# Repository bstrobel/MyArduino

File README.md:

# MyArduino
PCB to get my stock pile of 328s used as Arduino

Idee: Kleines generisches PCB bei Elecrow bestellten, um meine 328 einfach verbauen oder auf Steckbrett verwenden zu können.
- Größe um in direkt in kleines, günstiges Gehäuse verbaut werden zu können, das es bei Reichelt oder Conrad gibt
	- Gehäuse bei R heraussuchen, wenn Mindestgröße feststeht
- Pin Header mit Belegung und Bezeichnung wie bei Arduino, aber nicht notwendigerweise so angeordnet, dass Arduino Shields darauf passen. Aber eventuell so, dass Einsatz kleiner Shields für SD-Karten oder Sensoren nicht blockiert wird.
- Pin Header so anordnen, dass Verwendung auf Steckbrett möglich ist
- Stromversorgung:
	- Optionale Bestückung mit LM317 inkl. Justier-Rs und Block-Cs
	- auch MCP1702 (LDO 5v) Regler -> Achtung: nicht pinkompatibel mit 78L05!
	- Stromversorgungsheader für direkte Versorgung oder an Regler-IC
- ICP Header mit Standardbelegung
- Resettaster
- Arduino-LED an Port 13 vorsehen, muss ja nicht bestückt werden.
- Quarzbestückung vorsehen
	- aber Ports auch herausführen
- AREF-Cap: https://www.avrfreaks.net/forum/capacitor-aref-atmega328

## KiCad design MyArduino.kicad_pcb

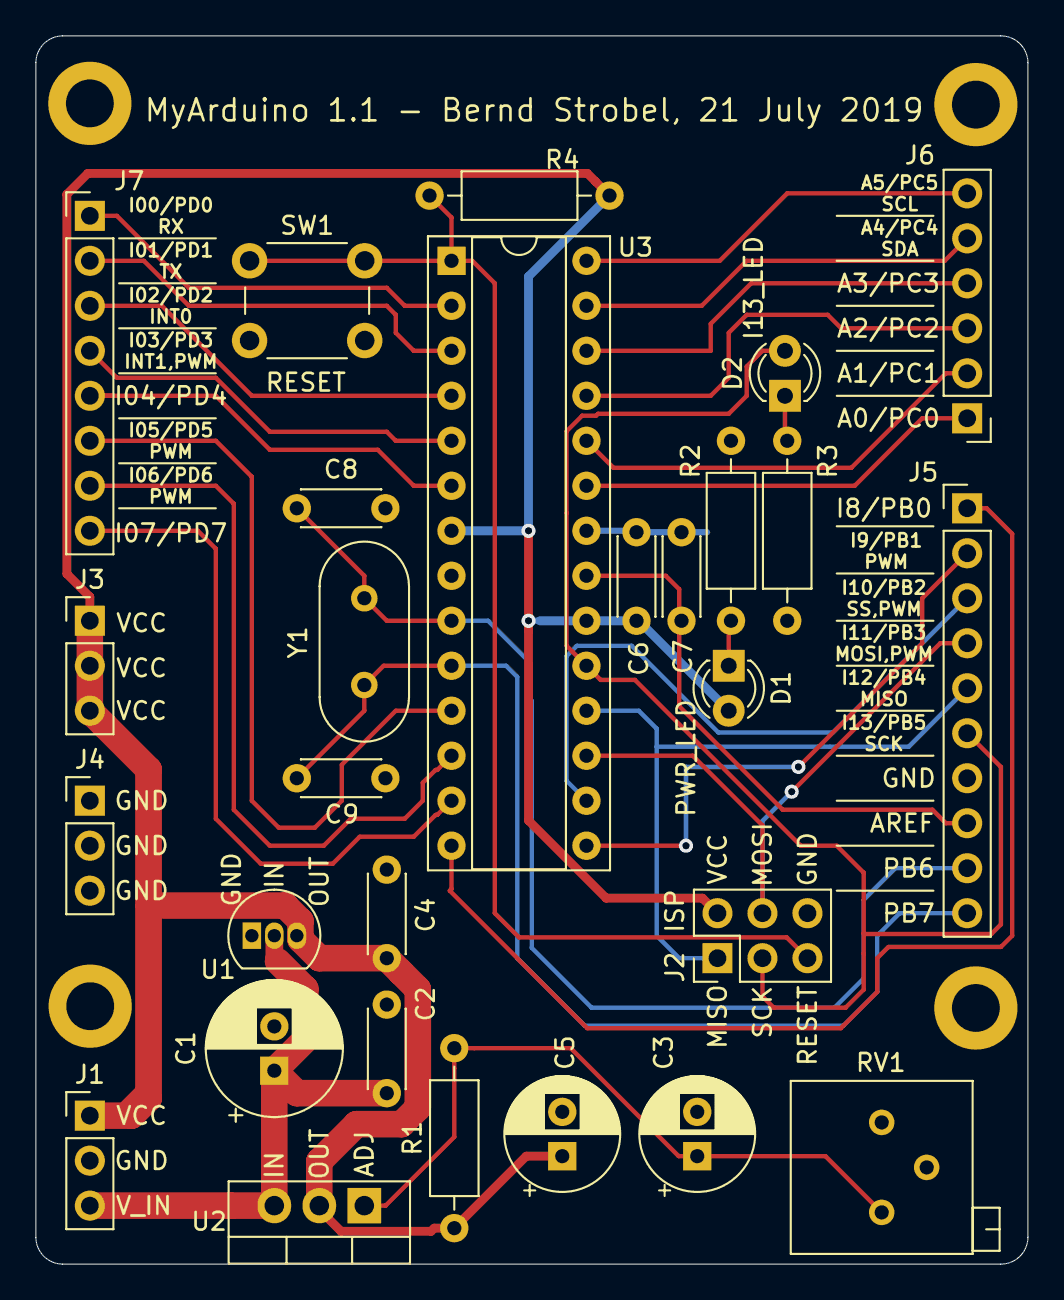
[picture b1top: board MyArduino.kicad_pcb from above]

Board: 2 copper layers, 56.0 x 69.3 mm, 32 parts (0 on the bottom side), 30 nets.

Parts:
C1: 100u; CP_Radial_D7.5mm_P2.50mm
C2, C4, C6: 100n; C_Disc_D4.3mm_W1.9mm_P5.00mm
C3: 10u; CP_Radial_D6.3mm_P2.50mm
C5: 22u; CP_Radial_D6.3mm_P2.50mm
C7: 10n; C_Disc_D4.3mm_W1.9mm_P5.00mm
C8, C9: 22p; C_Disc_D4.3mm_W1.9mm_P5.00mm
D1, D2: LED; LED_D3.0mm
J1: PWR; PinHeader_1x03_P2.54mm_Vertical
J2: ISP; PinHeader_2x03_P2.54mm_Vertical
J3: VCC; PinHeader_1x03_P2.54mm_Vertical
J4: GND; PinHeader_1x03_P2.54mm_Vertical
J5: IOH; PinHeader_1x10_P2.54mm_Vertical
J6: AD; PinHeader_1x06_P2.54mm_Vertical
J7: IOL; PinHeader_1x08_P2.54mm_Vertical
J8, J9, J10, J11: MountingHole_2.7mm_M2.5_DIN965_Pad
R1: 240R; R_Axial_DIN0207_L6.3mm_D2.5mm_P10.16mm_Horizontal
R2, R3: 470R; R_Axial_DIN0207_L6.3mm_D2.5mm_P10.16mm_Horizontal
R4: 10k; R_Axial_DIN0207_L6.3mm_D2.5mm_P10.16mm_Horizontal
RV1: 5k; Potentiometer_Bourns_3296P_Horizontal
SW1: SW_Push; SW_PUSH_6mm_H5mm
U1: MCP1700-5002E_TO92; TO-92_Inline
U2: LM317_TO220; TO-220-3_Vertical
U3: ATmega328P-PU; DIP-28_W7.62mm_Socket
Y1: 16MHz; Crystal_HC18-U_Vertical

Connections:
/AD0: J6.1, U3.23
/AD1: J6.2, U3.24
/AD2: J6.3, U3.25
/AD3: J6.4, U3.26
/AD4: J6.5, U3.27
/AD5: J6.6, U3.28
/AREF: C7.1, J5.8, U3.21
/IO0: J7.1, U3.2
/IO1: J7.2, U3.3
/IO2: J7.3, U3.4
/IO3: J7.4, U3.5
/IO4: J7.5, U3.6
/IO5: J7.6, U3.11
/IO6: J7.7, U3.12
/IO7: J7.8, U3.13
/IO8: J5.1, U3.14
/IO9: J5.2, U3.15
/MISO: J2.1, J5.5, U3.18
/MOSI: J2.4, J5.4, U3.17
/RESET: J2.5, R4.2, SW1.1, U3.1
/SCK: D2.2, J2.3, J5.6, U3.19
/SS: J5.3, U3.16
/V_UNREG: C1.1, C2.1, J1.3, U1.2, U2.3
/XTAL1_PB6: C8.1, J5.9, U3.9, Y1.1
/XTAL2_PB7: C9.1, J5.10, U3.10, Y1.2
GND: C1.2, C2.2, C3.2, C4.2, C5.2, C6.2, C7.2, C8.2, C9.2, J1.2, J2.6, J4.1, J4.2, J4.3, J5.7, J8.1, J9.1, J10.1, J11.1, R2.2, R3.2, RV1.2, RV1.3, SW1.2, U1.1, U3.8, U3.22
unnamed: C3.1, R1.2, RV1.1, U2.1
unnamed: D1.1, R2.1
unnamed: D2.1, R3.1
VCC: C4.1, C5.1, C6.1, D1.2, J1.1, J2.2, J3.1, J3.2, J3.3, R1.1, R4.1, U1.3, U2.2, U3.7, U3.20

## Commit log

2019-07-21 Version 1.0
    Ordered 5 pcs @ Elecrow today
2019-07-21 Improved routing and power traces width
    Version 1.1
